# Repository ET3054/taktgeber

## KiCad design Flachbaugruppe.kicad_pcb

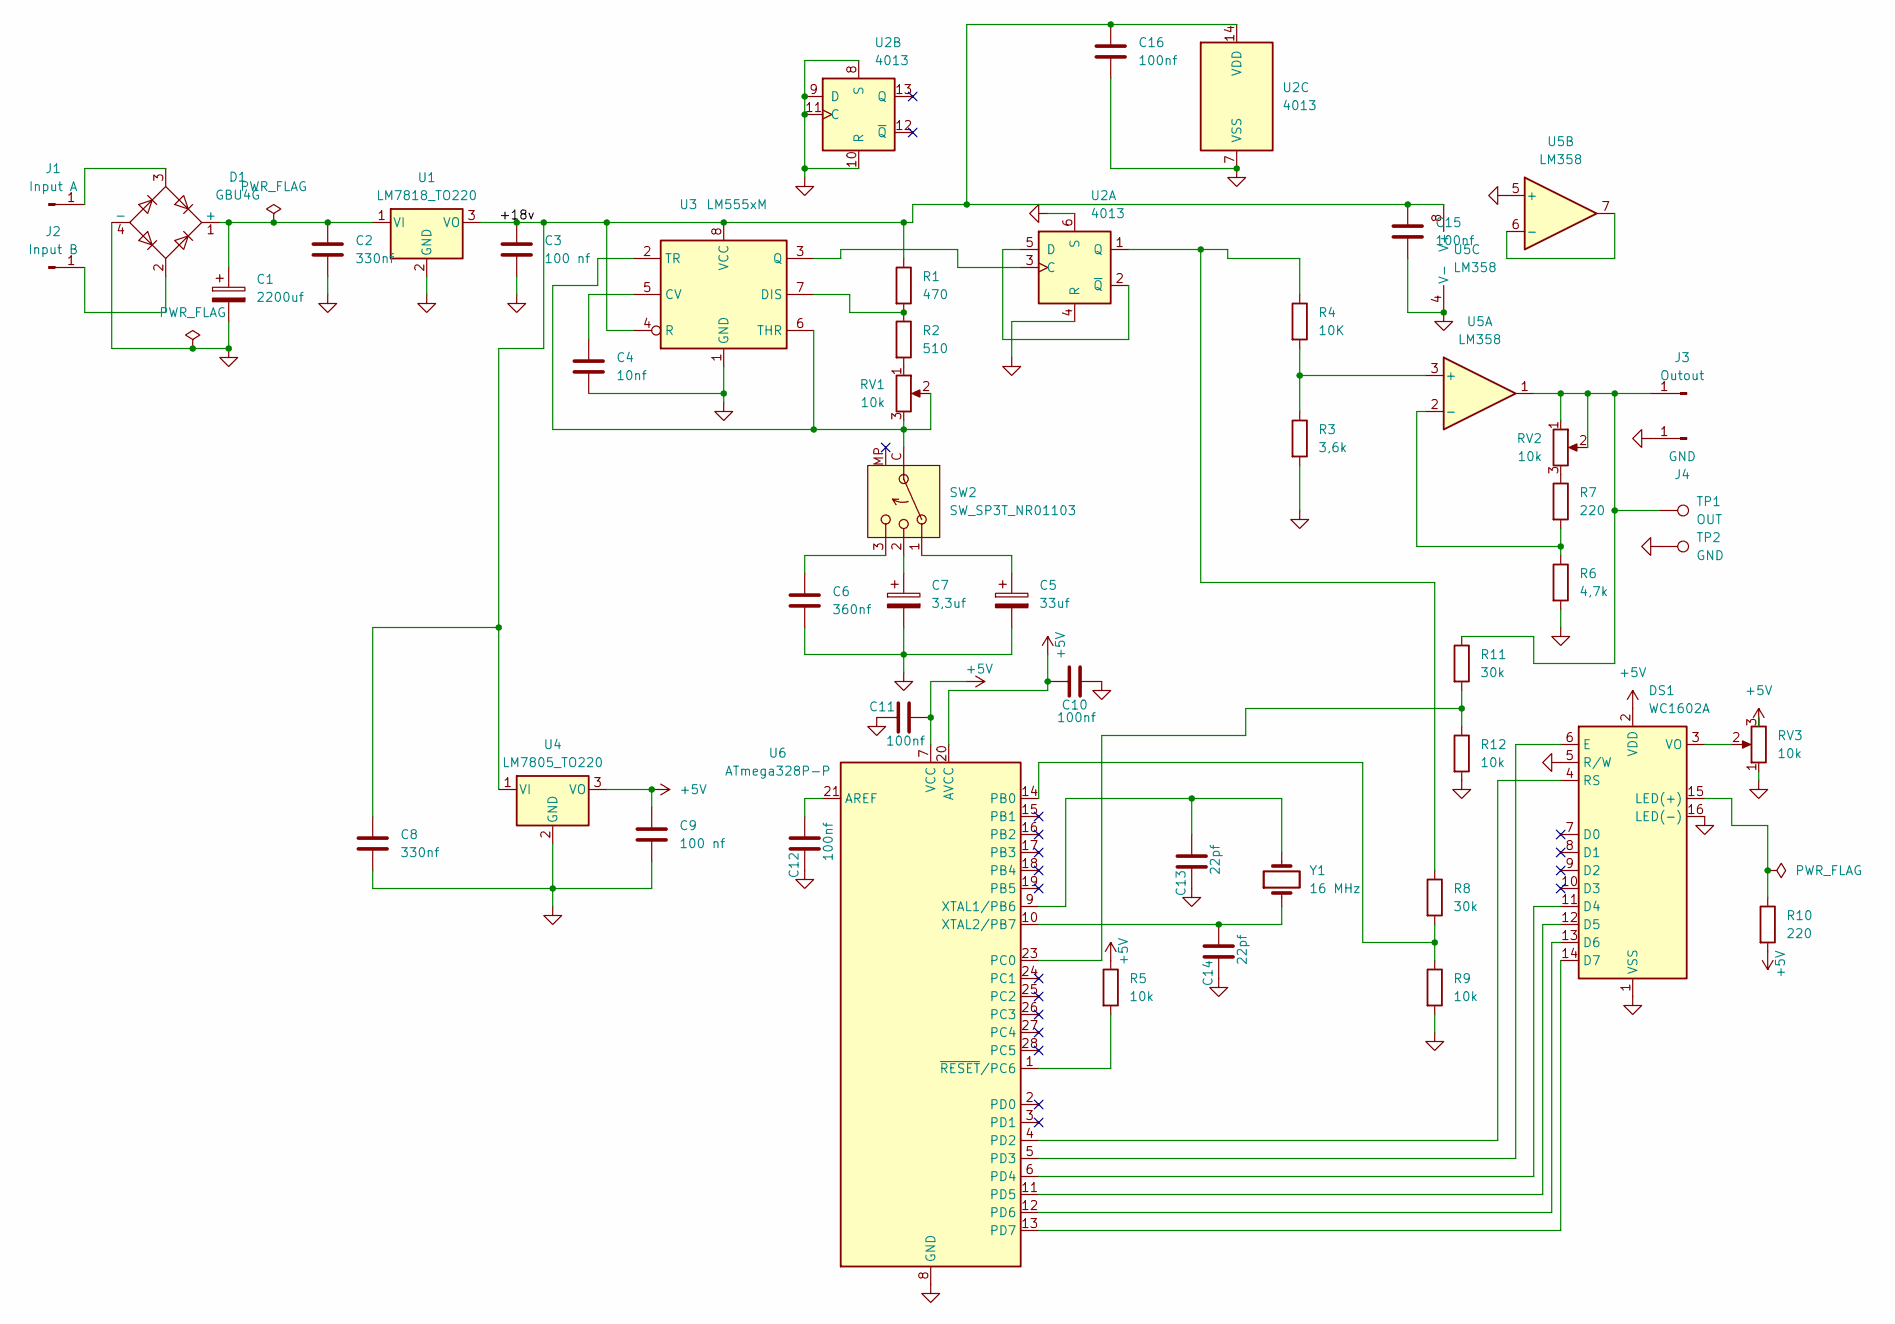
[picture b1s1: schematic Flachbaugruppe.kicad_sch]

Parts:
C1: 2200uf; CP_Radial_D16.0mm_P7.50mm
C2, C8: 330nf; C_0805_2012Metric
C3, C9: 100 nf; C_0805_2012Metric
C4: 10nf; C_0805_2012Metric
C5: 33uf; CP_Radial_D6.3mm_P2.50mm
C6: 360nf; C_0805_2012Metric
C7: 3,3uf; CP_Radial_D5.0mm_P2.00mm
C10, C11, C12, C15, C16: 100nf; C_0805_2012Metric
C13, C14: 22pf; C_0805_2012Metric
D1: GBU4G; Diode_Bridge_Vishay_GBU
DS1: WC1602A
J1: Input A; Banana_Jack_1Pin
J2: Input B; Banana_Jack_1Pin
J3: Outout; Banana_Jack_1Pin
J4: GND; Banana_Jack_1Pin
R1: 470; R_0805_2012Metric
R2: 510; R_0805_2012Metric
R3: 3,6k; R_0805_2012Metric
R4: 10K; R_0805_2012Metric
R5, R9, R12: 10k; R_0805_2012Metric
R6: 4,7k; R_0805_2012Metric
R7, R10: 220; R_0805_2012Metric
R8, R11: 30k; R_0805_2012Metric
RV1, RV2: 10k; Potentiometer_Alps_RK09K_Single_Horizontal
RV3: 10k; Potentiometer_Bourns_3296W_Vertical
SW2: SW_SP3T_NR01103; SW_NKK_NR01
TP1: OUT; TestPoint_Loop_D2.50mm_Drill1.0mm
TP2: GND; TestPoint_Loop_D2.50mm_Drill1.0mm
U1: LM7818_TO220; TO-220-3_Vertical
U2: 4013; DIP-14_W7.62mm
U3: LM555xM; DIP-8_W7.62mm
U4: LM7805_TO220; TO-220-3_Vertical
U5: LM358; DIP-8_W7.62mm
U6: ATmega328P-P; DIP-28_W7.62mm
Y1: 16 MHz; Crystal_HC49-U_Vertical

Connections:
+5V: C9.1, C10.1, C11.2, DS1.2 (VDD), R5.1, R10.2, RV3.3, U4.3 (VO), U6.7 (VCC), U6.20 (AVCC)
/+18v: C3.1, C8.1, C15.1, C16.1, R1.1, U1.3 (VO), U2.14 (VDD), U3.4 (R), U3.8 (VCC), U4.1 (VI), U5.8 (V+)
GND: C1.2, C2.2, C3.2, C4.2, C5.2, C6.2, C7.2, C8.2, C9.2, C10.2, C11.1, C12.1, C13.1, C14.1, C15.2, C16.2, D1.4 (-), DS1.1 (VSS), DS1.5 (R/W), DS1.16 (LED(-)), J4.1, R3.2, R6.2, R9.2, R12.2, RV3.1, TP2.1, U1.2 (GND), U2.4 (R), U2.6 (S), U2.7 (VSS), U2.8 (S), U2.9 (D), U2.10 (R), U2.11 (C), U3.1 (GND), U4.2 (GND), U5.4 (V-), U5.5 (+), U6.8 (GND), U6.22 (GND)
unnamed: C5.1, SW2.1
unnamed: C6.1, SW2.3
unnamed: C7.1, SW2.2
unnamed: C1.1, C2.1, D1.1 (+), U1.1 (VI)
unnamed: DS1.11 (D4), U6.6 (PD4)
unnamed: DS1.12 (D5), U6.11 (PD5)
unnamed: DS1.13 (D6), U6.12 (PD6)
unnamed: DS1.14 (D7), U6.13 (PD7)
unnamed: DS1.6 (E), U6.5 (PD3)
unnamed: DS1.15 (LED(+)), R10.1
unnamed: DS1.4 (RS), U6.4 (PD2)
unnamed: DS1.3 (VO), RV3.2
unnamed: D1.3, J1.1
unnamed: D1.2, J2.1
unnamed: J3.1, R11.1, RV2.1, RV2.2, TP1.1, U5.1
unnamed: R2.2, RV1.1
unnamed: R7.1, RV2.3
unnamed: RV1.2, RV1.3, SW2.C (Common), U3.2 (TR), U3.6 (THR)
unnamed: U2.3 (C), U3.3 (Q)
unnamed: U2.2 (~Q), U2.5 (D)
unnamed: R4.1, R8.1, U2.1 (Q)
unnamed: C4.1, U3.5 (CV)
unnamed: R1.2, R2.1, U3.7 (DIS)
unnamed: R3.1, R4.2, U5.3 (+)
unnamed: R6.1, R7.2, U5.2 (-)
unnamed: U5.6 (-), U5.7
unnamed: C12.2, U6.21 (AREF)
unnamed: R8.2, R9.1, U6.14 (PB0)
unnamed: R11.2, R12.1, U6.23 (PC0)
unnamed: C13.2, U6.9 (XTAL1/PB6), Y1.2
unnamed: C14.2, U6.10 (XTAL2/PB7), Y1.1
unnamed: R5.2, U6.1 (~RESET/PC6)

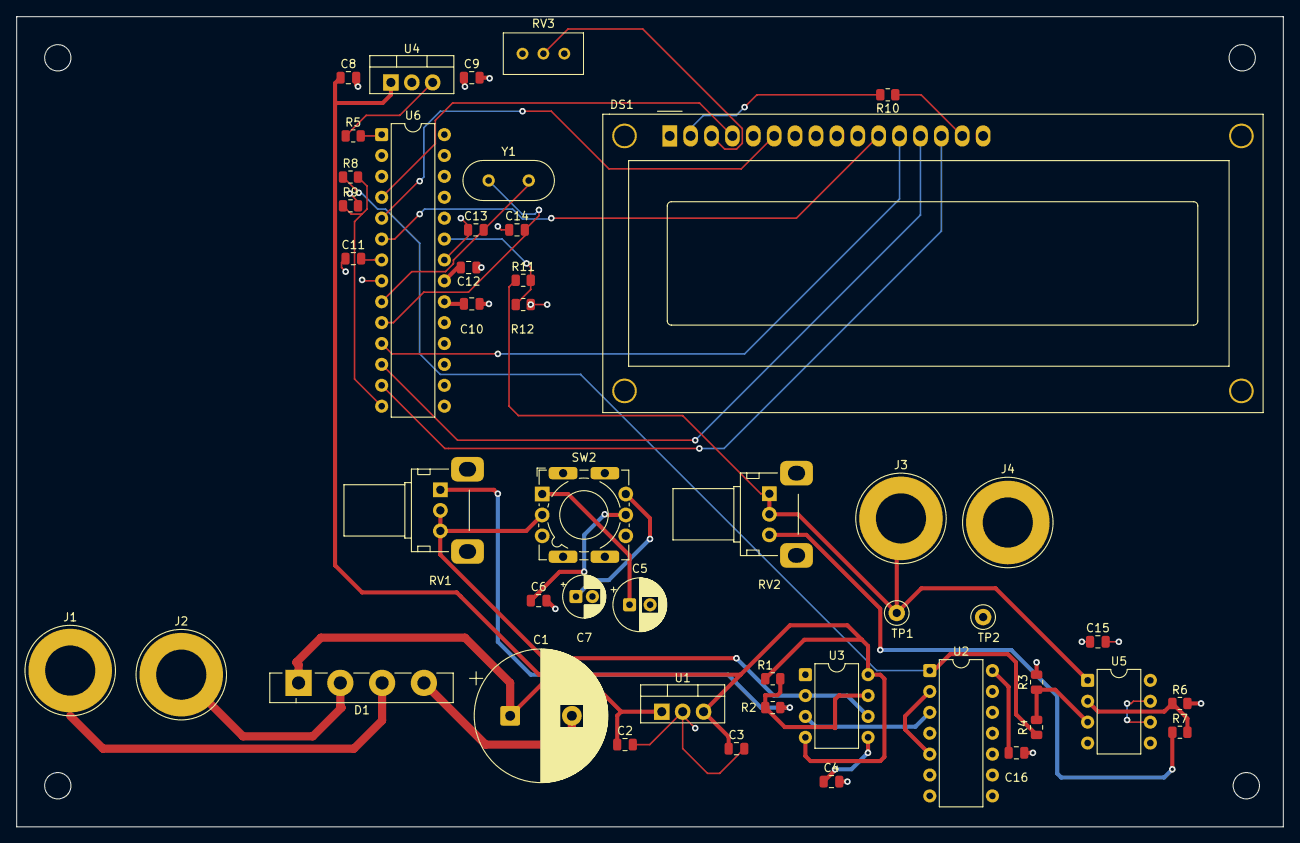
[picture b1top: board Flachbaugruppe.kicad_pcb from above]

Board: 4 copper layers, 154.0 x 98.5 mm, 51 parts (0 on the bottom side), 35 nets.

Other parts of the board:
H1, H2, H3, H4: MountingHole_3.2mm_M3

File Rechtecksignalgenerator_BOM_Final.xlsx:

RefDes | Qty | Value / Function | Manufacturer | MPN / Procurement spec | Assembly
D1 | 1 | Bridge rectifier | Vishay | GBU4G (supplier orderable suffix) | Populate
C1 | 1 | 2200uF / 50V | Nichicon | UHW1H222MHD | Populate
U1 | 1 | 18V regulator | STMicroelectronics | L7818CV | Populate
C2 | 1 | 330nF / 50V / X7R / 0805 | KEMET | C0805X334K5RACTU | Populate
C3,C9,C10,C11,C12,C15,C16 | 7 | 100nF / 50V / X7R / 0805 | KEMET | C0805C104K5RACTU | Populate
U3 | 1 | CMOS timer, 2-18V | Renesas | ICM7555IPAZ | Socket + IC
C4 | 1 | 10nF / 50V / X7R / 0805 | KEMET | C0805C103K5RACTU | Populate
R1 | 1 | 470R / 1% / 0805 | YAGEO | RC0805FR-07470RL | Populate
R2 | 1 | 510R / 1% / 0805 | YAGEO | RC0805FR-07510RL | Populate
RV1,RV2 | 2 | 10k linear | ALPS Alpine | RK09K1110AK4 | Populate
SW2 | 1 | 3-position rotary switch | NKK Switches | NR01103 | Populate
C6 | 1 | 360nF / >=50V / X7R / +/-10% / 0805 | Approved equivalent | Exact specification required | Populate
C7 | 1 | 3.3uF / 50V | Wurth Elektronik | 860020672007 | Populate
C5 | 1 | 33uF / 50V | Panasonic | EEUFC1H330 | Populate
U2 | 1 | Dual D flip-flop | Texas Instruments | CD4013BE | Socket + IC
R3 | 1 | 3.6k / 1% / 0805 | YAGEO | RC0805FR-073K6L | Populate
R4,R5,R9,R12 | 4 | 10k / 1% / 0805 | YAGEO | RC0805FR-0710KL | Populate
U5 | 1 | Dual op-amp | Texas Instruments | LM358P | Socket + IC
R6 | 1 | 4.7k / 1% / 0805 | YAGEO | RC0805FR-074K7L | Populate
R7,R10 | 2 | 220R / 1% / 0805 | YAGEO | RC0805FR-07220RL | Populate
U4 | 1 | 5V regulator | STMicroelectronics | L7805CV | Populate
U6 | 1 | ATmega328P, DIP-28 | Microchip | ATMEGA328P-PU | SUPPLY LOOSE - DO NOT INSERT
Y1 | 1 | 16MHz / CL about 16pF / HC49 THT | Approved manufacturer | Exact spec | Populate
C13,C14 | 2 | 22pF / 50V / C0G / 0805 | KEMET | C0805C220J5GACTU | Populate
DS1 | 1 | LCD 16x2 / 5V / HD44780-compatible | Approved equivalent | WC1602A mechanical spec | Populate
RV3 | 1 | 10k trimmer | Bourns | 3296W-1-103LF | Populate
R8,R11 | 2 | 30k / 1% / 0805 | YAGEO | RC0805FR-0730KL | Populate
J1-J4 | 4 | Banana jack footprints | - | DNP | DO NOT POPULATE
Sockets | 4 | 2x DIP-8 + DIP-14 + DIP-28 | Approved manufacturer | 2.54mm pitch / 7.62mm rows | Populate
